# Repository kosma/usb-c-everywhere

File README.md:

# I Put USB-C Everywhere

## (and you can't stop me)

This is my random collection of adapters and PCBs designed to make everything
in my lab USB-C compatible.

## [USB type B replacement](usb-b2c/)

Drop-in replacement for the old classic USB type B connector. Includes
a 3d-printed plastic part to match the connector shape.

## [Barrel Jack replacement](usb-c-barreljack/)

Drop-in replacement for the good old 5.5mm, barrel jack.

- Mostly fits in the existing footprints.
- Set to 12V/3A by default.
- Puts the USB-C connector at the correct height by stacking three PCBs together.
- Allows for both positive and negative polarity, depending on the bottom PCB used.
- Voltage and current negotiation parameters can be changed by modifying resistor straps.
- Subject to limitations of USB-C PD - for example, an Apple charger can't output 12V.

## [Isolated UART, 1.8-5.5V](usb-c-serial/)

Serial port adapter with two control lines (RTS and DTR), 1.5kV isolated.
The initial use was programming ESP8266 but comes useful in many other scenarios.

## [3Dconnexion CadMouse](usb-c-cadmouse/)

Replacement PCB for the 3Dconnexion CadMouse. Originally Micro USB.
Requires some milling to fit the new PCB.

## [3Dconnexion SpaceMouse](usb-c-spacemouse/)

Replacement PCB for the 3Dconnexion SpaceMouse. Originally Micro USB.
Includes a 3D-printed plastic part.

## FAQ

- Q: What's the USB connector on these designs?  
  A: My current goto connector is [GCT USB4105-GF-A](https://octopart.com/search?q=USB4105-GF-A).
  It's cheap and good. The WE equivalent is [629722000214](https://www.we-online.com/en/components/products/WR-COM_USB_20_TYPE_C_RECEPTACLE_HORIZONTAL_SMT#629722000214).
  Other manufacturers most probably have equivalent connectors - this is
  the de-facto standard footprint for USB-C 2.0.

- Q: Why?  
  A:

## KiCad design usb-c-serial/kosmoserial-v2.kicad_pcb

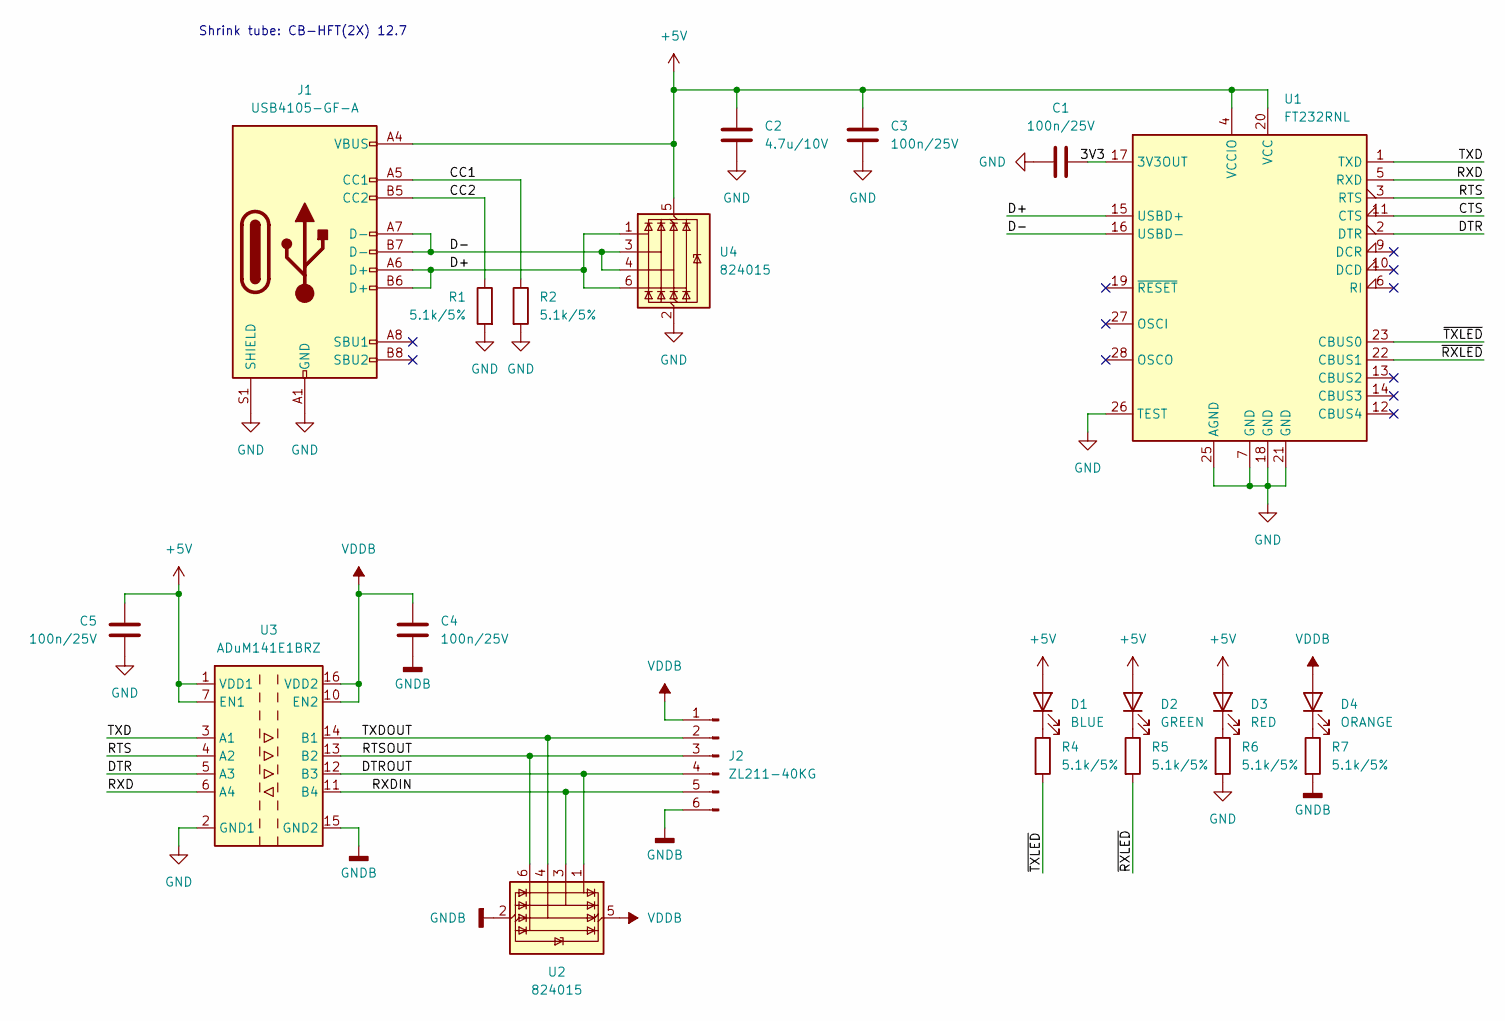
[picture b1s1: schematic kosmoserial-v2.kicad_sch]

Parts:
C1, C3, C4, C5: 100n/25V; C_0603_1608Metric
C2: 4.7u/10V; C_0805_2012Metric
D1: BLUE; LED_0603_1608Metric
D2: GREEN; LED_0603_1608Metric
D3: RED; LED_0603_1608Metric
D4: ORANGE; LED_0603_1608Metric
J1: USB4105-GF-A; USB_C_Receptacle_GCT_USB4105-xx-A_16P_TopMnt_Horizontal
J2: ZL211-40KG; PinHeader_1x06_P2.54mm_Horizontal
R1, R2, R4, R5, R6, R7: 5.1k/5%; R_0603_1608Metric
U1: FT232RNL; SSOP-28_5.3x10.2mm_P0.65mm
U2, U4: 824015; SOT-23-6
U3: ADuM141E1BRZ; SOIC-16_3.9x9.9mm_P1.27mm

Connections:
+5V: C2.1, C3.2, C5.2, D1.2 (A), D2.2 (A), D3.2 (A), J1.A4 (VBUS), J1.A9 (VBUS), J1.B4 (VBUS), J1.B9 (VBUS), U1.4 (VCCIO), U1.20 (VCC), U3.1 (VDD1), U3.7 (EN1), U4.5 (VBUS)
/3V3: C1.2, U1.17 (3V3OUT)
/CC1: J1.A5 (CC1), R2.1
/CC2: J1.B5 (CC2), R1.1
/CTS: U1.11 (CTS)
/D+: J1.A6 (D+), J1.B6 (D+), U1.15 (USBD+), U4.1 (I/O1), U4.6 (I/O4)
/D-: J1.A7 (D-), J1.B7 (D-), U1.16 (USBD-), U4.3 (I/O2), U4.4 (I/O3)
/DTR: U1.2 (DTR), U3.5 (A3)
/DTROUT: J2.4, U2.1 (I/O1), U3.12 (B3)
/RTS: U1.3 (RTS), U3.4 (A2)
/RTSOUT: J2.3, U2.6 (I/O4), U3.13 (B2)
/RXD: U1.5 (RXD), U3.6 (A4)
/RXDIN: J2.5, U2.3 (I/O2), U3.11 (B4)
/TXD: U1.1 (TXD), U3.3 (A1)
/TXDOUT: J2.2, U2.4 (I/O3), U3.14 (B1)
/~RXLED: R5.2, U1.22 (CBUS1)
/~TXLED: R4.2, U1.23 (CBUS0)
GND: C1.1, C2.2, C3.1, C5.1, J1.A1 (GND), J1.A12 (GND), J1.B1 (GND), J1.B12 (GND), J1.S1 (SHIELD), R1.2, R2.2, R6.2, U1.7 (GND), U1.18 (GND), U1.21 (GND), U1.25 (AGND), U1.26 (TEST), U3.2 (GND1), U3.8 (GND1), U4.2 (GND)
GNDB: C4.1, J2.6, R7.2, U2.2 (GND), U3.9 (GND2), U3.15 (GND2)
unnamed: D1.1 (K), R4.1
unnamed: D2.1 (K), R5.1
unnamed: D3.1 (K), R6.1
unnamed: D4.1 (K), R7.1
VDDB: C4.2, D4.2 (A), J2.1, U2.5 (VBUS), U3.10 (EN2), U3.16 (VDD2)

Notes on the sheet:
Shrink tube: CB-HFT(2X) 12.7

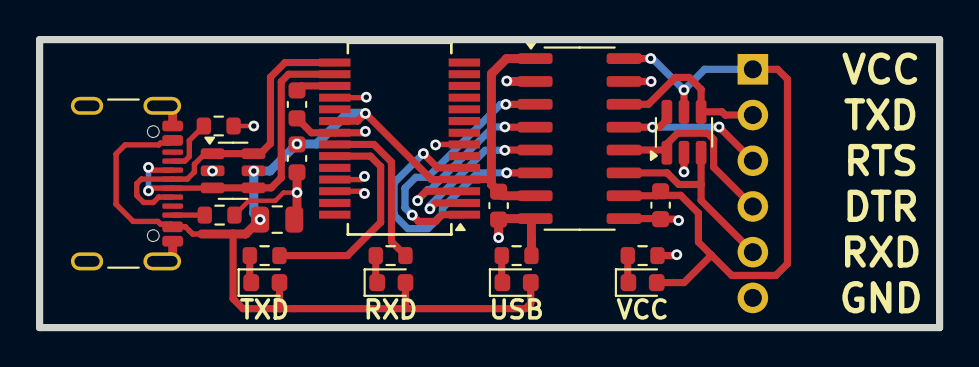
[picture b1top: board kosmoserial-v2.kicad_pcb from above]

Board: 2 copper layers, 50.0 x 16.0 mm, 21 parts (0 on the bottom side), 23 nets.

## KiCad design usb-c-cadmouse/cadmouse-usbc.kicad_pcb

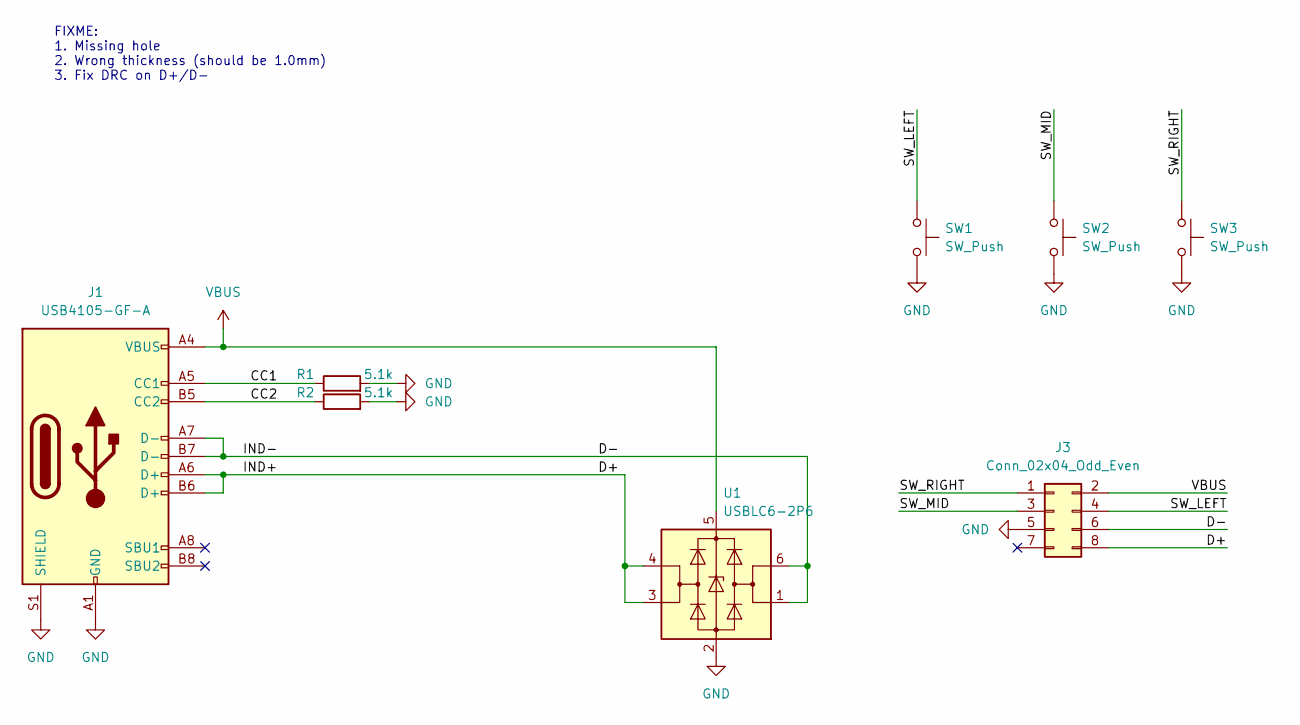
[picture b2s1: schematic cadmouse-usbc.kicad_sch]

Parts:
J1: USB4105-GF-A; USB_C_Receptacle_GCT_USB4105-xx-A_16P_TopMnt_Horizontal
J3: Conn_02x04_Odd_Even; PinHeader_2x04_P1.27mm_Vertical
R1, R2: 5.1k; R_0402_1005Metric
SW1, SW2, SW3: SW_Push; D2FC
U1: USBLC6-2P6; SOT-666

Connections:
/CC1: J1.A5 (CC1), R1.1
/CC2: J1.B5 (CC2), R2.1
/D+: J1.A6 (D+), J1.B6 (D+), J3.8, U1.3 (I/O2), U1.4 (I/O2)
/D-: J1.A7 (D-), J1.B7 (D-), J3.6, U1.1 (I/O1), U1.6 (I/O1)
/SW_LEFT: J3.4, SW1.2
/SW_MID: J3.3, SW2.2
/SW_RIGHT: J3.1, SW3.2
GND: J1.A1 (GND), J1.A12 (GND), J1.B1 (GND), J1.B12 (GND), J1.S1 (SHIELD), J3.5, R1.2, R2.2, SW1.1, SW2.1, SW3.1, U1.2 (GND)
VBUS: J1.A4 (VBUS), J1.A9 (VBUS), J1.B4 (VBUS), J1.B9 (VBUS), J3.2, U1.5 (VBUS)

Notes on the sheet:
FIXME: 1. Missing hole 2. Wrong thickness (should be 1.0mm) 3. Fix DRC on D+/D-

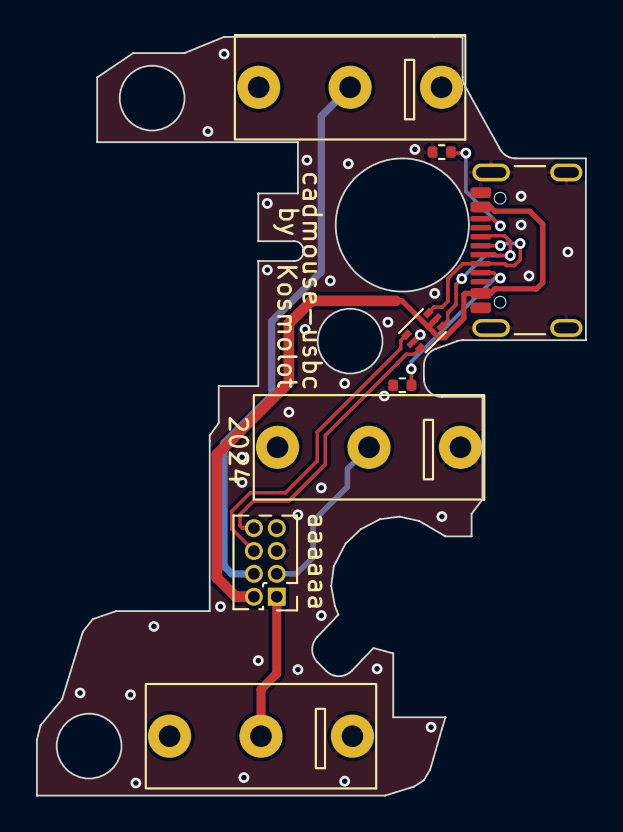
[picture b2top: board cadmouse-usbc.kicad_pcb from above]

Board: 2 copper layers, 30.5 x 42.2 mm, 8 parts (0 on the bottom side), 9 nets.

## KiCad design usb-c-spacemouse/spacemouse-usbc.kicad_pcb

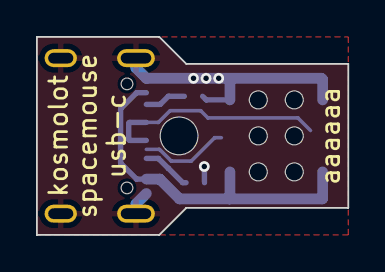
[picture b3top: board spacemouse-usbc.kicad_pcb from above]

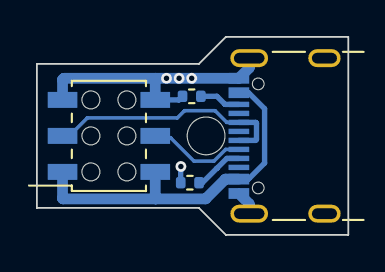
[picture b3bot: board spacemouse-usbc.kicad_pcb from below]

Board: 2 copper layers, 17.3 x 11.0 mm, 4 parts (4 on the bottom side), 6 nets.

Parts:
J1: USB4105-GF-A; USB_C_Receptacle_GCT_USB4105-xx-A_16P_TopMnt_Horizontal
J2: Conn_02x03_Odd_Even; PinSocket_2x03_P2.00mm_Vertical_SMD
R1, R2: 5.1k; R_0402_1005Metric

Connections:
/CC1: J1.A5 (CC1), R1.1
/CC2: J1.B5 (CC2), R2.1
/D+: J1.A6 (D+), J1.B6 (D+), J2.3
/D-: J1.A7 (D-), J1.B7 (D-), J2.4
GND: J1.A1 (GND), J1.A12 (GND), J1.B1 (GND), J1.B12 (GND), J1.S1 (SHIELD), J2.5, J2.6, R1.2, R2.2
VBUS: J1.A4 (VBUS), J1.A9 (VBUS), J1.B4 (VBUS), J1.B9 (VBUS), J2.1, J2.2

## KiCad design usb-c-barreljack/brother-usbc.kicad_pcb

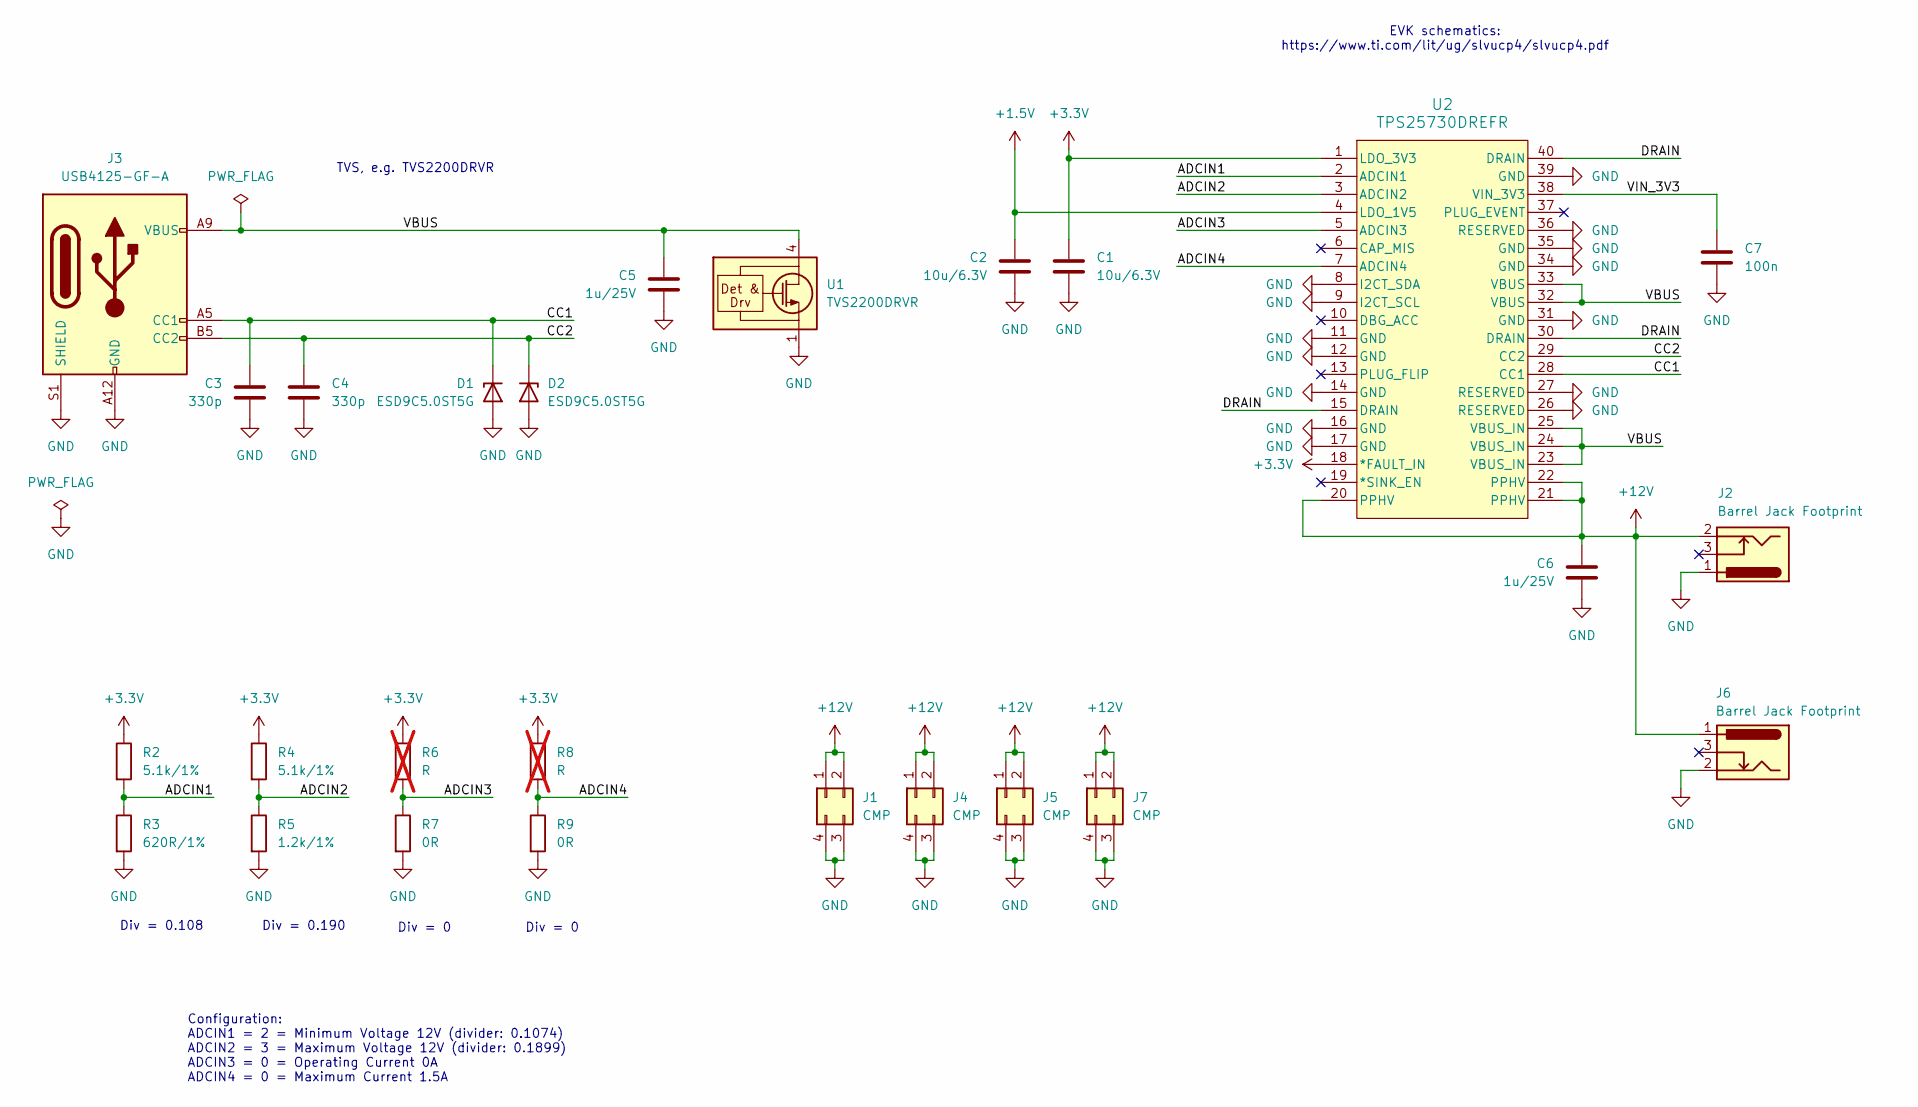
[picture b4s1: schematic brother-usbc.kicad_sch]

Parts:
C1, C2: 10u/6.3V; C_0603_1608Metric
C3, C4: 330p; C_0201_0603Metric
C5, C6: 1u/25V; C_0603_1608Metric
C7: 100n; C_0201_0603Metric
D1, D2: ESD9C5.0ST5G; D_SOD-923
J1, J4, J5, J7: CMP
J2, J6: Barrel Jack Footprint; BarrelJack_Horizontal
J3: USB4125-GF-A; USB_C_Receptacle_GCT_USB4125-xx-x-0190_6P_TopMnt_Horizontal
R2, R4: 5.1k/1%; R_0201_0603Metric
R3: 620R/1%; R_0201_0603Metric
R5: 1.2k/1%; R_0201_0603Metric
R6, R8: R; R_0201_0603Metric; not fitted
R7, R9: 0R; R_0201_0603Metric
U1: TVS2200DRVR; WSON-6-1EP_2x2mm_P0.65mm_EP1x1.6mm
U2: TPS25730DREFR; WQFN38_REF_TEX

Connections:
+1.5V: C2.1, U2.4 (LDO_1V5)
+3.3V: C1.1, R2.1, R4.1, R6.1, R8.1, U2.1 (LDO_3V3), U2.18 (*FAULT_IN)
+12V: C6.1, J1.1, J1.2, J2.2, J4.1, J4.2, J5.1, J5.2, J6.1, J7.1, J7.2, U2.20 (PPHV), U2.21 (PPHV), U2.22 (PPHV)
/ADCIN1: R2.2, R3.1, U2.2 (ADCIN1)
/ADCIN2: R4.2, R5.1, U2.3 (ADCIN2)
/ADCIN3: R6.2, R7.1, U2.5 (ADCIN3)
/ADCIN4: R8.2, R9.1, U2.7 (ADCIN4)
/CC1: C3.1, D1.1 (K), J3.A5 (CC1), U2.28 (CC1)
/CC2: C4.1, D2.1 (K), J3.B5 (CC2), U2.29 (CC2)
/DRAIN: U2.15 (DRAIN), U2.30 (DRAIN), U2.40 (DRAIN)
/VBUS: C5.1, J3.A9 (VBUS), J3.B9 (VBUS), U1.4 (IN), U1.5 (IN), U1.6 (IN), U2.23 (VBUS_IN), U2.24 (VBUS_IN), U2.25 (VBUS_IN), U2.32 (VBUS), U2.33 (VBUS)
/VIN_3V3: C7.1, U2.38 (VIN_3V3)
GND: C1.2, C2.2, C3.2, C4.2, C5.2, C6.2, C7.2, D1.2 (A), D2.2 (A), J1.3, J1.4, J2.1, J3.A12 (GND), J3.B12 (GND), J3.S1 (SHIELD), J4.3, J4.4, J5.3, J5.4, J6.2, J7.3, J7.4, R3.2, R5.2, R7.2, R9.2, U1.1 (GND), U1.2 (GND), U1.3 (GND), U1.7 (GND), U2.8 (I2CT_SDA), U2.9 (I2CT_SCL), U2.11 (GND), U2.12 (GND), U2.14 (GND), U2.16 (GND), U2.17 (GND), U2.26 (RESERVED), U2.27 (RESERVED), U2.31 (GND), U2.34 (GND), U2.35 (GND), U2.36 (RESERVED), U2.39 (GND)

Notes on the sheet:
Div = 0
Configuration: ADCIN1 = 2 = Minimum Voltage 12V (divider: 0.1074) ADCIN2 = 3 = Maximum Voltage 12V (divider: 0.1899) ADCIN3 = 0 = Operating Current 0A ADCIN4 = 0 = Maximum Current 1.5A
Div = 0.190
TVS, e.g. TVS2200DRVR
EVK schematics: https://www.ti.com/lit/ug/slvucp4/slvucp4.pdf
Div = 0.108

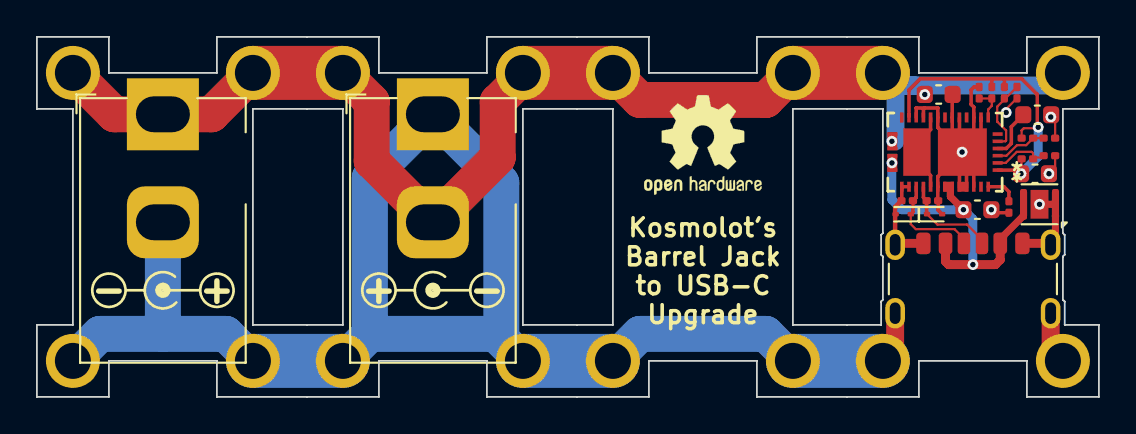
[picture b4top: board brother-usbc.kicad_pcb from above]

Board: 2 copper layers, 59.0 x 20.0 mm, 26 parts (0 on the bottom side), 13 nets.

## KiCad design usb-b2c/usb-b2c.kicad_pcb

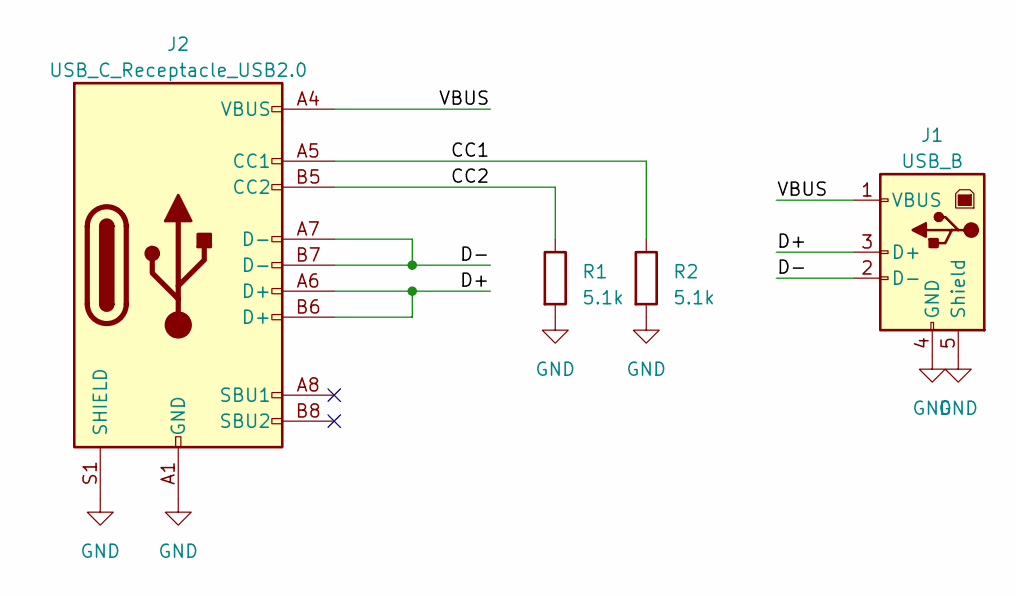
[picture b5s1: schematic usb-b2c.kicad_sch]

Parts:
J1: USB_B; USB_B_Lumberg_2411_02_Horizontal
J2: USB_C_Receptacle_USB2.0; USB_C_Receptacle_GCT_USB4105-xx-A_16P_TopMnt_Horizontal
R1, R2: 5.1k; R_0603_1608Metric

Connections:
/CC1: J2.A5 (CC1), R2.1
/CC2: J2.B5 (CC2), R1.1
/D+: J1.3 (D+), J2.A6 (D+), J2.B6 (D+)
/D-: J1.2 (D-), J2.A7 (D-), J2.B7 (D-)
/VBUS: J1.1 (VBUS), J2.A4 (VBUS), J2.A9 (VBUS), J2.B4 (VBUS), J2.B9 (VBUS)
GND: J1.4 (GND), J1.5 (Shield), J2.A1 (GND), J2.A12 (GND), J2.B1 (GND), J2.B12 (GND), J2.S1 (SHIELD), R1.2, R2.2

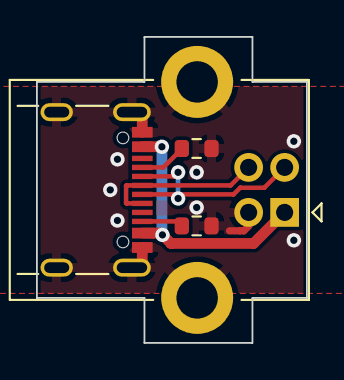
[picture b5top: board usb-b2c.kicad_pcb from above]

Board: 2 copper layers, 15.0 x 17.0 mm, 4 parts (0 on the bottom side), 6 nets.

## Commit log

2024-10-29 add README
2024-10-29 usb-b2c: move to a subdirectory
2024-10-29 usb-b2c: add plastic cover
2024-10-29 usb-b2c: add to README
2024-10-29 .gitignore: import from https://raw.githubusercontent.com/github/gitignore/main/KiCad.gitignore
2024-10-29 README.md: add FAQ about connector models
2024-10-29 README.md: fix formatting of FAQ
2024-10-29 usb-c-barreljack: add design files
2024-10-29 usb-c-barreljack: add to README
2024-10-29 add spacemouse & cadmouse
2024-10-29 add usb-serial
2024-10-29 README.md: add links
2024-10-29 README.md: add note about USB PD
